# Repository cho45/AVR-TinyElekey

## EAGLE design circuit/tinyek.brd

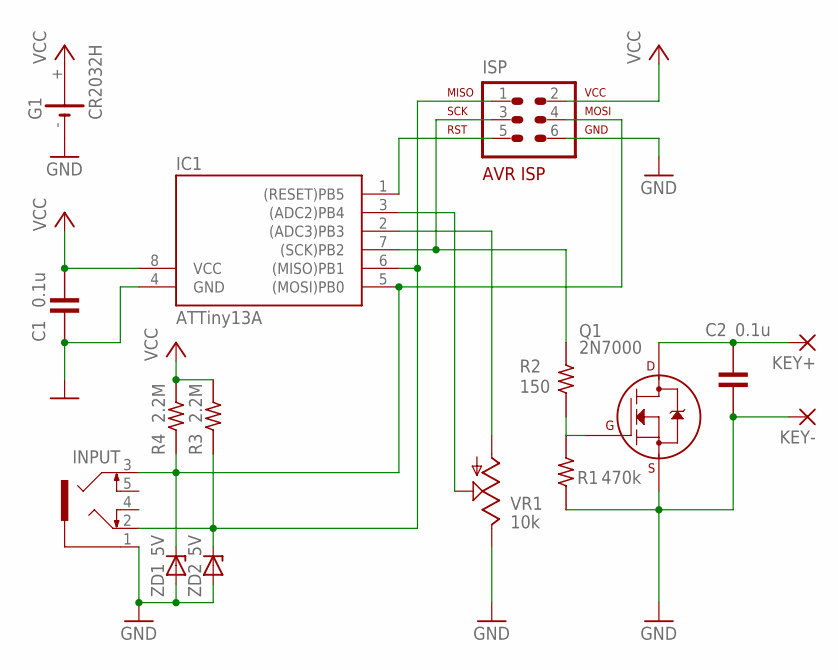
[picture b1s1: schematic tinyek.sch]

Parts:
C1, C2: 0.1u; 50-0302-5.08
G1: CR2032H
IC1: ATTiny13A; DIL08
INPUT: 1503_09
ISP: AVR-ISP-6VERT; AVR-ISP-6
KEY+: 2,15/1,0
KEY-: 2,15/1,0
Q1: 2N7000; TO-92
R1: 470k; 1/4W-2.54V
R2: 150; 1/4W-2.54V
R3, R4: 2.2M; 1/4W-7.62H
VR1: 10k; B25U
ZD1, ZD2: 5V; DO35Z10

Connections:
GND: C1.PAD1 (1), C2.PAD2 (2), G1.-, IC1.4 (GND), INPUT.1, ISP.6, KEY-.1, Q1.1 (S), R1.PAD2 (2), VR1.E, ZD1.A, ZD2.A
unnamed: IC1.1 ((RESET)PB5), ISP.5
unnamed: IC1.7 ((SCK)PB2), ISP.3, R2.PAD1 (1)
unnamed: IC1.2 ((ADC3)PB3), VR1.A
unnamed: IC1.3 ((ADC2)PB4), VR1.S
unnamed: Q1.2 (G), R1.PAD1 (1), R2.PAD2 (2)
unnamed: C2.PAD1 (1), KEY+.1, Q1.3 (D)
unnamed: IC1.5 ((MOSI)PB0), INPUT.3, ISP.4, R4.PAD2 (2), ZD1.C
unnamed: IC1.6 ((MISO)PB1), INPUT.2, ISP.1, R3.PAD2 (2), ZD2.C
VCC: C1.PAD2 (2), G1.+, IC1.8 (VCC), ISP.2, R3.PAD1 (1), R4.PAD1 (1)

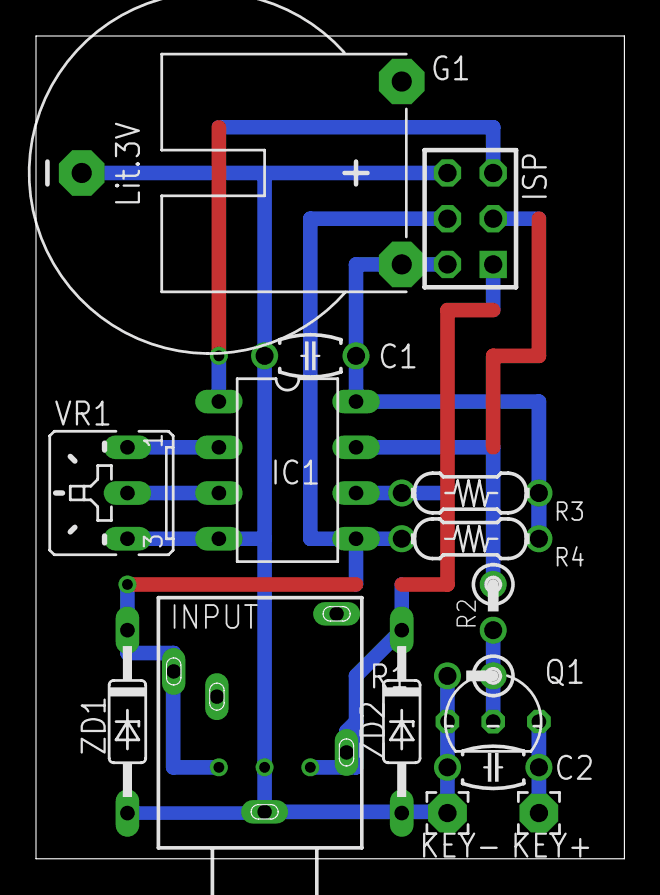
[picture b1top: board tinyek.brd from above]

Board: 2 copper layers, 32.7 x 45.7 mm, 16 parts (0 on the bottom side), 10 nets.

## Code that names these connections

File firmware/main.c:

#include <avr/io.h>
#include <avr/interrupt.h>
#include <util/delay.h>
#include <avr/sleep.h>

#define nop asm volatile("nop")
#define clear_bit(v, bit) v &= ~(1 << bit)
#define set_bit(v, bit)   v |=  (1 << bit)

#define INPUT_DOT PB0
#define INPUT_DASH PB1
#define OUTPUT_KEY PB2
#define ADC_VR PB3
#define ADC_SPEED 2

#define SPEED_MAX 30
#define SPEED_MIN 10

#define INHIBIT_RATE 0.3
#define INHIBIT_TIME(speed) ((uint16_t)(1200 * INHIBIT_RATE) / speed)
#define INHIBIT_AFTER(speed) ((uint16_t)(1200 * (1 - INHIBIT_RATE)) / speed)

#define CLOCK_DEVIDE 1.0
#define TIMER_INTERVAL (1.0 / (F_CPU / CLOCK_DEVIDE) * 1000)
#define INTERVAL_UNIT_IN_MS (uint16_t)(1.0 / TIMER_INTERVAL + 0.5)
#define DURATION(msec) (uint16_t)(msec * INTERVAL_UNIT_IN_MS)
#define NOW ((timer<<8)|TCNT0)

#define LONG_TIMER_INTERVAL (1.0 / (F_CPU / CLOCK_DEVIDE / 256) * 1000)
#define LONG_DURATION(msec) (uint16_t)(msec / LONG_TIMER_INTERVAL)

#define TIMER_INTERVAL_UNIT_IN_US (1.0 / (F_CPU / CLOCK_DEVIDE) * 1000)

#define VCC 3.3
#define ADC_MAX 1024L
#define ADC_VOLT(mV) ((uint16_t)(ADC_MAX / (VCC * 1000)) * mV)
#define ADC_PERCENT(result) (result * 100L / ADC_MAX)

uint8_t dot_keying, dash_keying;
uint8_t speed;
uint8_t unit;

volatile uint8_t timer;
volatile uint16_t idle;
volatile uint16_t adc_interval;

uint16_t do_adc (uint8_t channel) {
	uint16_t ret;
	ADCSRA =
		(1<<ADEN)  | // Enable (Turn on ADC)
		(0<<ADATE) | // Auto Trigger Enable
		(0<<ADIF)  | // Interrupt Flag
		(1<<ADIE)  | // Interrupt Enable
		001        ; // Prescale

	//ADCSRB = 0;

	ADMUX =
		(0<<REFS0) | // Use VCC ref
		(0<<ADLAR) | // Right Adjust
		channel;

	// START
	set_bit(ADCSRA, ADSC); 
	set_sleep_mode(SLEEP_MODE_ADC);
	while (bit_is_set(ADCSRA, ADSC)) sleep_mode();

	// Read ADCL first, it locks ADCH register until ADCH is read.
	ret = (ADCL) | ((ADCH) << 8);

	// Clear All and turn off ADC
	ADCSRA = 0;

	return ret;
}

ISR(ADC_vect) { }

// max 501ms
void delay_ms(uint16_t t) {
	uint16_t end;
	uint16_t end0;
	cli();
	timer = 0; TCNT0 = 0;
	end = NOW + DURATION(t);
	end0 = end - 0x100;
	sei();
	while (NOW <= end0) {
		set_sleep_mode(SLEEP_MODE_IDLE);
		sleep_mode();
	}
	while (NOW <= end) { }
}

static inline void start_output() {
	set_bit(PORTB, OUTPUT_KEY);
}

static inline void stop_output() {
	clear_bit(PORTB, OUTPUT_KEY);
}


static inline void setup_io () {
	timer = 0;
	idle  = LONG_DURATION(10000);
	adc_interval = LONG_DURATION(1000);

	// 0=INPUT 1=OUTPUT
	DDRB   = (1<<OUTPUT_KEY)|(1<<ADC_VR);
	// 1=PULL-UP
	PORTB  = 0b00000000;

	// ADC2(PB4) の Digital Input を無効化 (省電力)
	DIDR0  = (1<<ADC2D);

	// Timer0 を分周なしで有効化
	TCCR0A = 0b00000000;
	TCCR0B = 0b00000001;

	// Timer0 割込みを許可
	TIMSK0  = (1<<TOIE0);

	// Pin-Change Interrupt Enable
	// パワーダウンからの復帰用
	GIMSK   = (1<<PCIE);
	// Paddle 接続ピンを Pin-Change 割込み対象に
	PCMSK   = (1<<PCINT1)|(1<<PCINT0);

	sei();
}

int main(void) {
	setup_io();

	for (;;) {
		if (adc_interval >= LONG_DURATION(1000)) {
			// ADC 用のボリュームに電圧をかける
			set_bit(PORTB, ADC_VR);
			speed = ADC_PERCENT(do_adc(ADC_SPEED)) * (SPEED_MAX - SPEED_MIN) / 100 + SPEED_MIN;
			// 解除
			clear_bit(PORTB, ADC_VR);
			unit  = 1200 / speed;
			adc_interval = 0;
		}

		if (dot_keying) {
			start_output();
			delay_ms(unit);
			stop_output();
			delay_ms(INHIBIT_TIME(speed));
			dot_keying = 0;
			delay_ms(INHIBIT_AFTER(speed));
			idle = 0;
		}

		if (dash_keying) {
			start_output();
			delay_ms(unit * 3);
			stop_output();
			delay_ms(INHIBIT_TIME(speed));
			dash_keying = 0;
			delay_ms(INHIBIT_AFTER(speed));
			idle = 0;
		}

		// 10000msec 経ったらパワーダウン
		if (idle > LONG_DURATION(10000)) {
			timer = 0;
			set_sleep_mode(SLEEP_MODE_PWR_DOWN);
			sleep_mode();
			adc_interval = LONG_DURATION(1000);
		} else {
			set_sleep_mode(SLEEP_MODE_IDLE);
			sleep_mode();
		}
	}
}

ISR(TIM0_OVF_vect) {
	timer++;
	idle++;
	adc_interval++;

	if (bit_is_clear(PINB, INPUT_DOT)) {
		dot_keying = 1;
	}

	if (bit_is_clear(PINB, INPUT_DASH)) {
		dash_keying = 1;
	}
}

ISR(PCINT0_vect) {
	idle = 0;
}

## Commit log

2013-10-27 init
2013-10-29 省電力化 (ADC中以外はボリュームに電流を流さない)
2013-10-29 F_CPU change to 600Mhz for low energy
2013-10-29 128khz
2013-10-29 comment
2013-10-30 うーん……… やっぱりときどきおかしいのでリセットをかけるように
2013-11-01 プルアップ抵抗を外部に出して消費電力おさえ
2013-11-02 eagle
2013-11-05 ADC sleep
2013-11-05 circuit
2013-11-07 ピンによってドライブ能力が違うので、一応余裕がある配置に設計変更。ほんと意味はないと思う
2013-11-07 測定しなおし
2013-11-07 update circuit
2013-11-07 電流制限抵抗を追加
